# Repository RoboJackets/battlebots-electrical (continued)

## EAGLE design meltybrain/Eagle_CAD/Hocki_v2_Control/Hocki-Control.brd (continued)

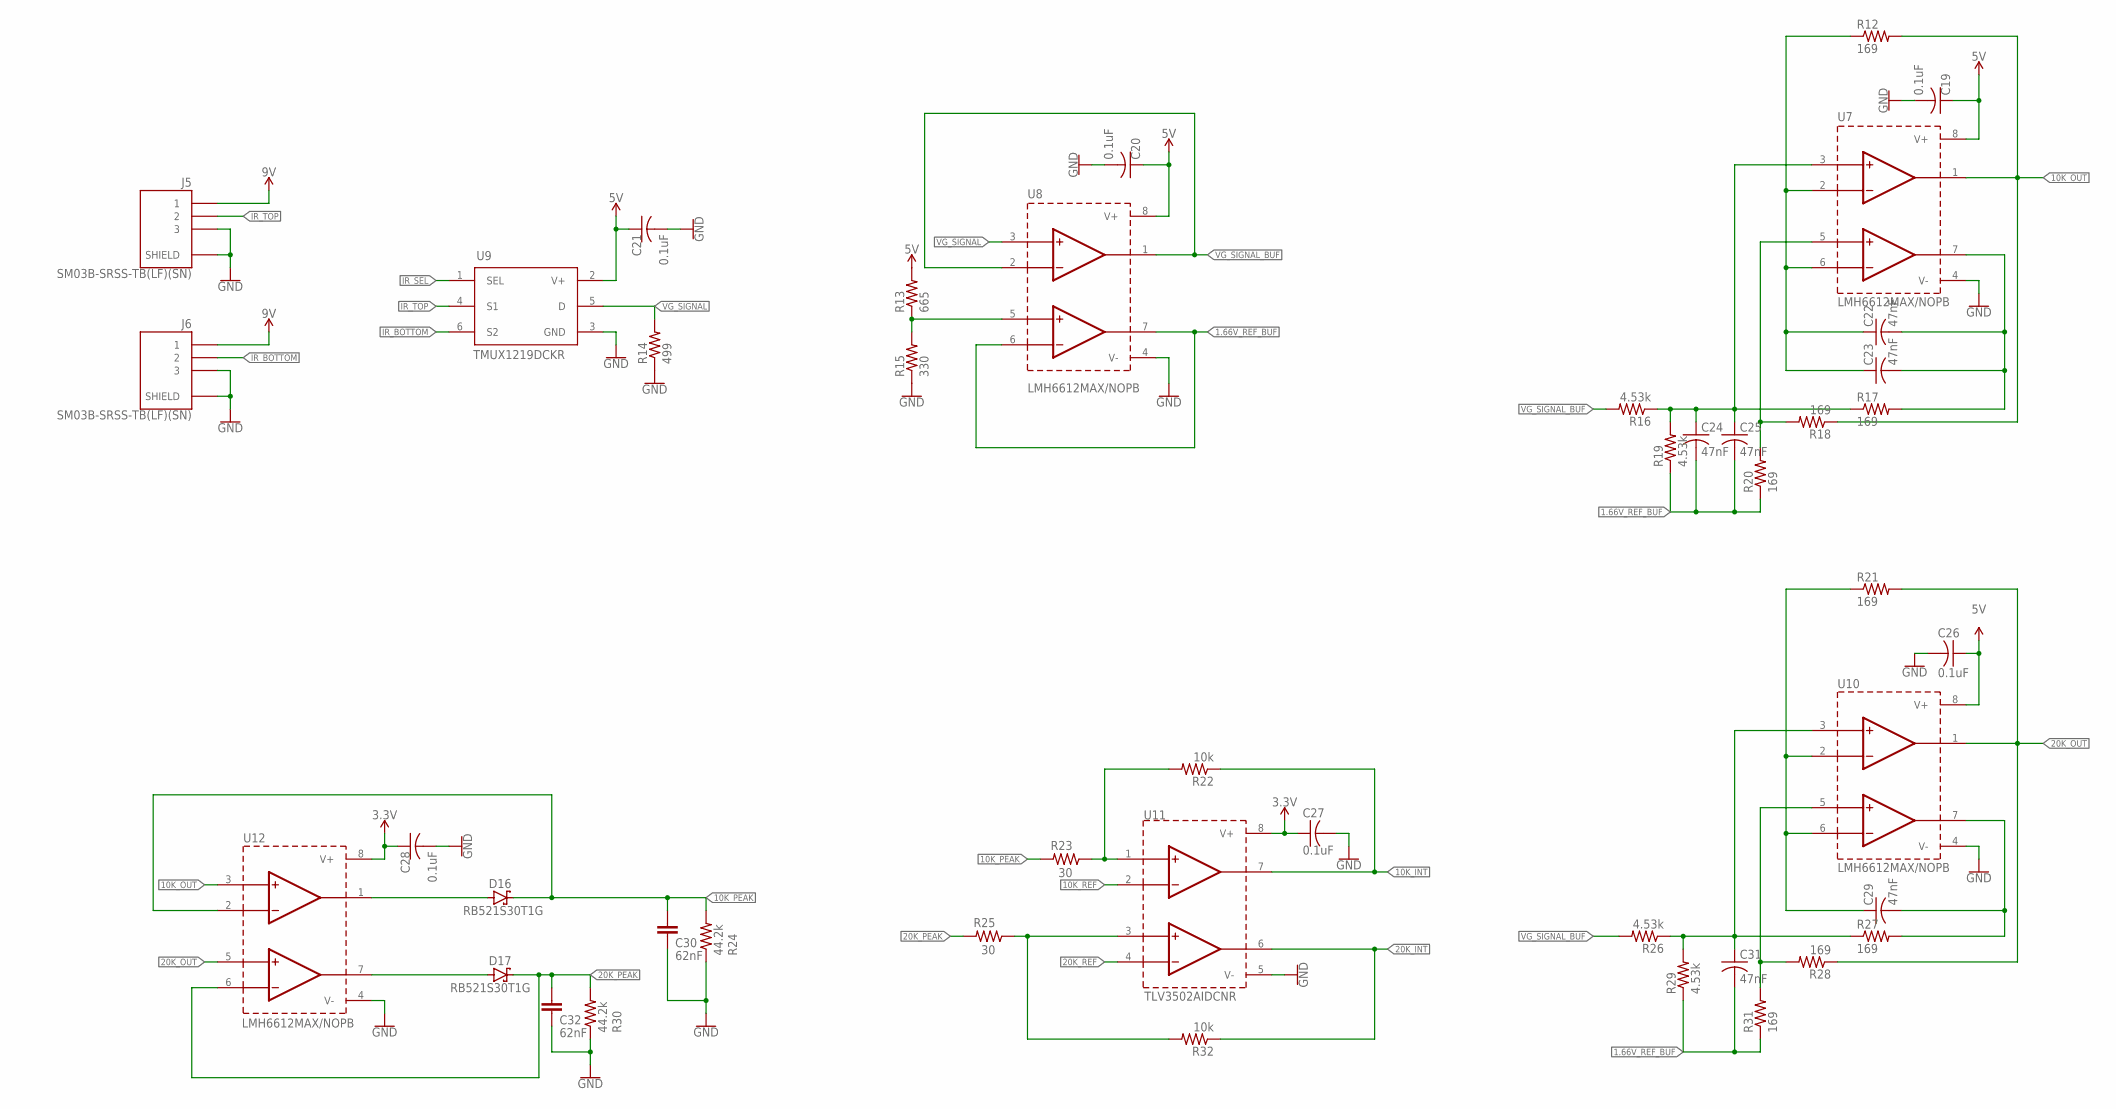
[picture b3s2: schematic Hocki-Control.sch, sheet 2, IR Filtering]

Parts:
C19, C20, C21, C26, C27, C28: 0.1uF; C0603
C22, C23, C24, C25, C29, C31: 47nF; C1206
C30, C32: 62nF; BFC241646203
D16, D17: RB521S30T1G; SOD-523
J5, J6: SM03B-SRSS-TB(LF)(SN)
R12, R17, R18, R20, R21, R27, R28, R31: 169; R0603
R13: 665; R0603
R14: 499; R0603
R15: 330; R0603
R16, R19, R26, R29: 4.53k; R0603
R22, R32: 10k; R0603
R23, R25: 30; R0603
R24, R30: 44.2k; R0603
U7, U8, U10, U12: LMH6612MAX/NOPB; 8-SOIC
U9: TMUX1219DCKR; SOT-363
U11: TLV3502AIDCNR; SOT-23-8

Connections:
1.6V_REF: R13.1, R15.2, U8.5 (INB+)
1.66V_REF_BUF: C24.2, C25.2, C31.2, R19.1, R20.1, R29.1, R31.1, U8.6 (INB-), U8.7 (OUTB)
3.3V: C27.1, C28.1, U11.8 (V+), U12.8 (V+); also elsewhere on the board
5V: C19.1, C20.1, C21.1, C26.1, R13.2, U7.8 (V+), U8.8 (V+), U9.2 (V+), U10.8 (V+); also elsewhere on the board
9V: J5.1, J6.1; also elsewhere on the board
10K_FB: C22.2, C23.2, R17.2, U7.7 (OUTB)
10K_IN: C24.1, C25.1, R16.1, R17.1, R19.2, U7.3 (INA+)
10K_INT: R22.1, U11.7 (OUTA); also elsewhere on the board
10K_OUT: R12.2, R18.1, U7.1 (OUTA), U12.3 (INA+)
10K_PEAK: C30.1, D16.1 (C), R23.2, R24.2, U12.2 (INA-); also elsewhere on the board
10K_REF: U11.2 (INA-); also elsewhere on the board
20K_FB: C29.2, R27.2, U10.7 (OUTB)
20K_IN: C31.1, R26.1, R27.1, R29.2, U10.3 (INA+)
20K_INT: R32.1, U11.6 (OUTB); also elsewhere on the board
20K_OUT: R21.2, R28.1, U10.1 (OUTA), U12.5 (INB+)
20K_PEAK: C32.1, D17.1 (C), R25.2, R30.2, U12.6 (INB-); also elsewhere on the board
20K_REF: U11.4 (INB-); also elsewhere on the board
GND: C19.2, C20.2, C21.2, C26.2, C27.2, C28.2, C30.2, C32.2, J5.3, J5.S1 (SHIELD), J5.S2 (SHIELD), J6.3, J6.S1 (SHIELD), J6.S2 (SHIELD), R14.1, R15.1, R24.1, R30.1, U7.4 (V-), U8.4 (V-), U9.3 (GND), U10.4 (V-), U11.5 (V-), U12.4 (V-); also elsewhere on the board
IR_BOTTOM: J6.2, U9.6 (S2)
IR_SEL: U9.1 (SEL); also elsewhere on the board
IR_TOP: J5.2, U9.4 (S1)
unnamed: D16.2 (A), U12.1 (OUTA)
unnamed: C22.1, C23.1, R12.1, U7.2 (INA-), U7.6 (INB-)
unnamed: R22.2, R23.1, U11.1 (INA+)
unnamed: R25.1, R32.2, U11.3 (INB+)
unnamed: R18.2, R20.2, U7.5 (INB+)
unnamed: D17.2 (A), U12.7 (OUTB)
unnamed: C29.1, R21.1, U10.2 (INA-), U10.6 (INB-)
unnamed: R28.2, R31.2, U10.5 (INB+)
VG_SIGNAL: R14.2, U8.3 (INA+), U9.5 (D)
VG_SIGNAL_BUF: R16.2, R26.2, U8.1 (OUTA), U8.2 (INA-)

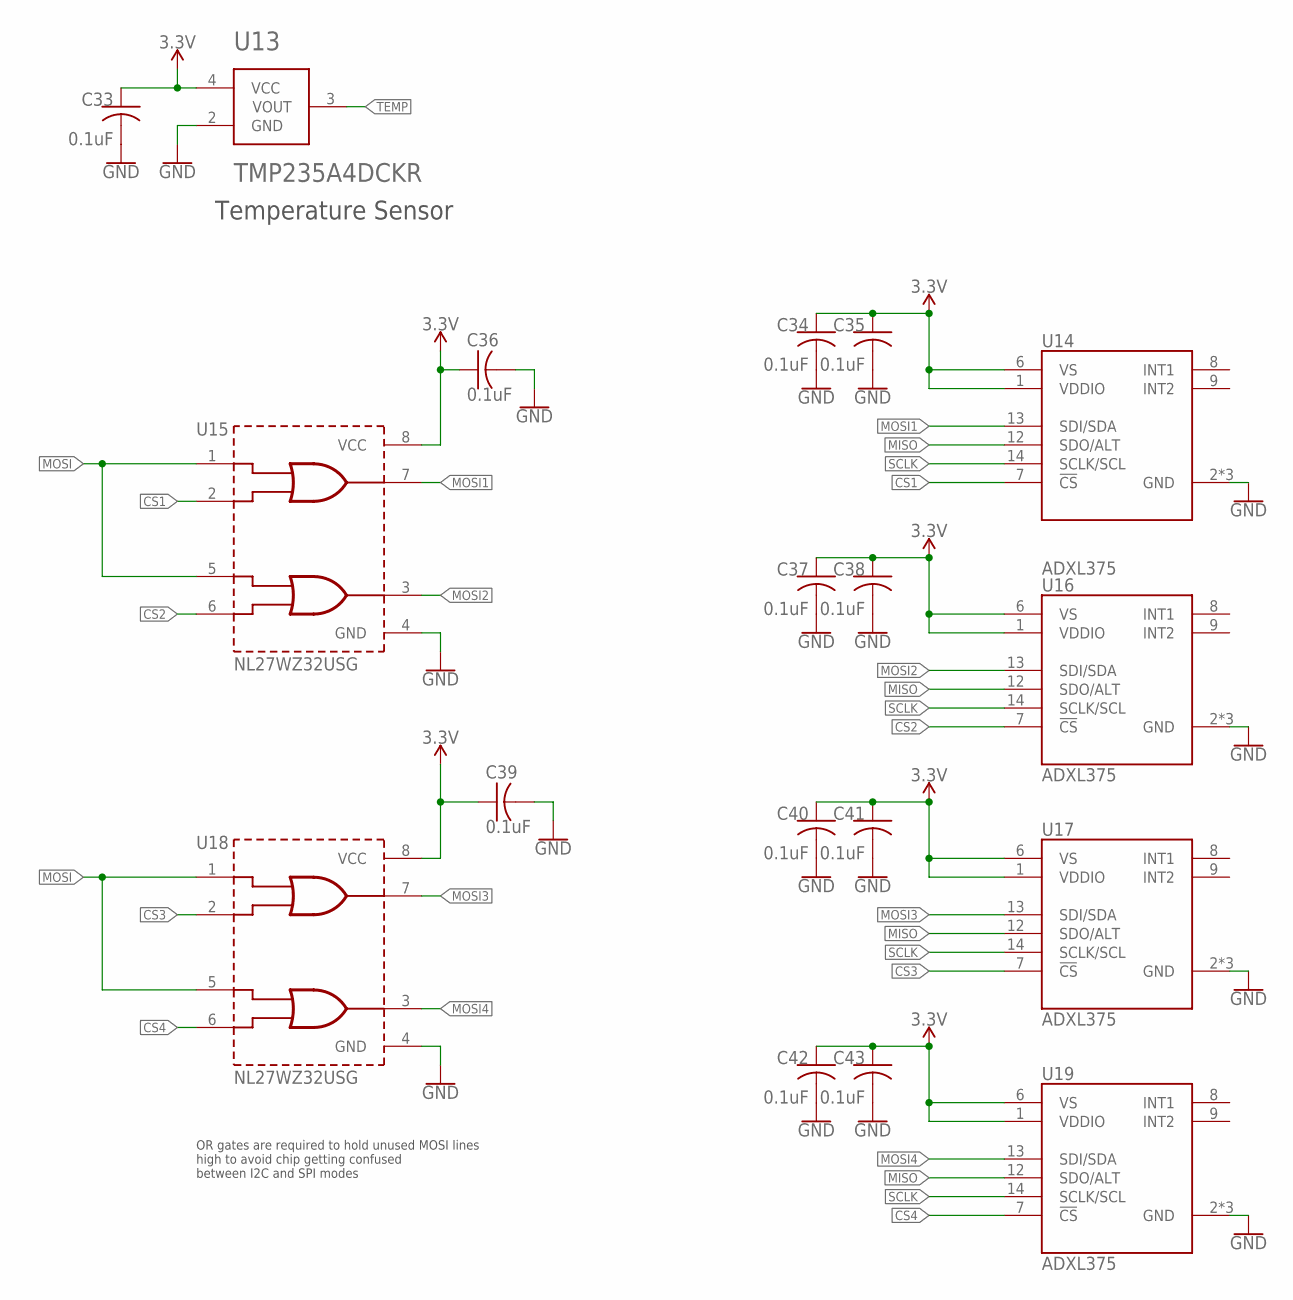
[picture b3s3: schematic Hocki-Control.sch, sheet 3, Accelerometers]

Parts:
C33, C34, C35, C36, C37, C38, C39, C40, C41, C42, C43: 0.1uF; C0603
U13: TMP235A4DCKR; SOT-353
U14, U16, U17, U19: ADXL375; 14-LGA
U15, U18: NL27WZ32USG; US8

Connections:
3.3V: C33.1, C34.1, C35.1, C36.1, C37.1, C38.1, C39.1, C40.1, C41.1, C42.1, C43.1, U13.4 (VCC), U14.1 (VDDIO), U14.6 (VS), U15.8 (VCC), U16.1 (VDDIO), U16.6 (VS), U17.1 (VDDIO), U17.6 (VS), U18.8 (VCC), U19.1 (VDDIO), U19.6 (VS); also elsewhere on the board
CS1: U14.7 (!CS), U15.2 (B1); also elsewhere on the board
CS2: U15.6 (B2), U16.7 (!CS); also elsewhere on the board
CS3: U17.7 (!CS), U18.2 (B1); also elsewhere on the board
CS4: U18.6 (B2), U19.7 (!CS); also elsewhere on the board
GND: C33.2, C34.2, C35.2, C36.2, C37.2, C38.2, C39.2, C40.2, C41.2, C42.2, C43.2, U13.2 (GND), U14.2 (GND), U14.4 (GND), U14.5 (GND), U15.4 (GND), U16.2 (GND), U16.4 (GND), U16.5 (GND), U17.2 (GND), U17.4 (GND), U17.5 (GND), U18.4 (GND), U19.2 (GND), U19.4 (GND), U19.5 (GND); also elsewhere on the board
MISO: U14.12 (SDO/ALT), U16.12 (SDO/ALT), U17.12 (SDO/ALT), U19.12 (SDO/ALT); also elsewhere on the board
MOSI: U15.1 (A1), U15.5 (A2), U18.1 (A1), U18.5 (A2); also elsewhere on the board
MOSI1: U14.13 (SDI/SDA), U15.7 (Y1)
MOSI2: U15.3 (Y2), U16.13 (SDI/SDA)
MOSI3: U17.13 (SDI/SDA), U18.7 (Y1)
MOSI4: U18.3 (Y2), U19.13 (SDI/SDA)
SCLK: U14.14 (SCLK/SCL), U16.14 (SCLK/SCL), U17.14 (SCLK/SCL), U19.14 (SCLK/SCL); also elsewhere on the board
TEMP: U13.3 (VOUT); also elsewhere on the board

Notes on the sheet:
OR gates are required to hold unused MOSI lines high to avoid chip getting confused between I2C and SPI modes
Temperature Sensor

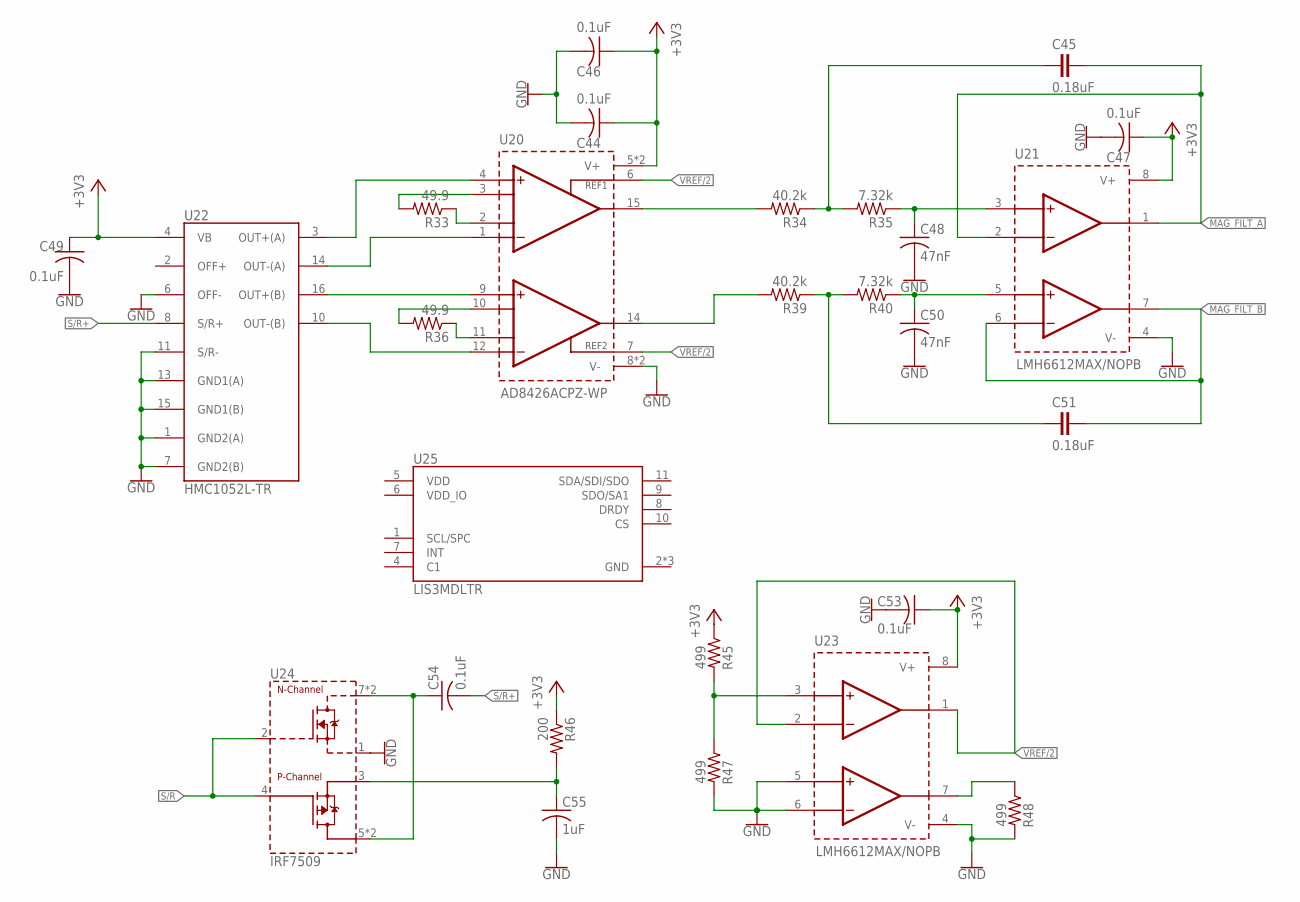
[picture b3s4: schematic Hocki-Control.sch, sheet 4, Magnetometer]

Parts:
C44, C46, C47, C49, C53, C54: 0.1uF; C0603
C45, C51: 0.18uF; ECH-U1H184GX9
C48, C50: 47nF; C1206
C55: 1uF; C0603
R33, R36: 49.9; R0603
R34, R39: 40.2k; R0603
R35, R40: 7.32k; R0603
R45, R47, R48: 499; R0603
R46: 200; R0603
U20: AD8426ACPZ-WP; 16LFCSP
U21, U23: LMH6612MAX/NOPB; 8-SOIC
U22: HMC1052L-TR; 16-LCC
U24: IRF7509; MICRO8
U25: LIS3MDLTR; LGA-12_2X2X1_STM

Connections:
+3V3: C44.1, C46.1, C47.1, C49.1, C53.1, R45.1, R46.1, U20.5 (V+), U20.16 (V+), U21.8 (V+), U22.4 (VB), U23.8 (V+); also elsewhere on the board
GND: C44.2, C46.2, C47.2, C48.2, C49.2, C50.2, C53.2, C55.2, R47.2, R48.2, U20.8 (V-), U20.13 (V-), U21.4 (V-), U22.1 (GND2(A)), U22.6 (OFF-), U22.7 (GND2(B)), U22.11 (S/R-), U22.13 (GND1(A)), U22.15 (GND1(B)), U23.4 (V-), U23.5 (INB+), U23.6 (INB-), U24.1 (S1); also elsewhere on the board
MAG_FILT_A: C45.2, U21.1 (OUTA), U21.2 (INA-); also elsewhere on the board
MAG_FILT_B: C51.2, U21.6 (INB-), U21.7 (OUTB); also elsewhere on the board
unnamed: C54.1, U24.5 (D2), U24.6 (D2), U24.7 (D1), U24.8 (D1)
unnamed: R45.2, R47.1, U23.3 (INA+)
unnamed: R48.1, U23.7 (OUTB)
unnamed: C45.1, R34.1, R35.2
unnamed: C48.1, R35.1, U21.3 (INA+)
unnamed: C51.1, R39.1, R40.2
unnamed: C50.1, R40.1, U21.5 (INB+)
unnamed: U20.4 (INA+), U22.3 (OUT+(A))
unnamed: U20.1 (INA-), U22.14 (OUT-(A))
unnamed: U20.9 (INB+), U22.16 (OUT+(B))
unnamed: U20.12 (INB-), U22.10 (OUT-(B))
unnamed: R39.2, U20.14 (OUTB)
unnamed: R34.2, U20.15 (OUTA)
unnamed: R33.2, U20.3 (RGA+)
unnamed: R33.1, U20.2 (RGA-)
unnamed: R36.2, U20.10 (RGB+)
unnamed: R36.1, U20.11 (RGB-)
S/R: U24.2 (G1), U24.4 (G2); also elsewhere on the board
S/R+: C54.2, U22.8 (S/R+)
VREF/2: U20.6 (REFA), U20.7 (REFB), U23.1 (OUTA), U23.2 (INA-)
VSR: C55.1, R46.2, U24.3 (S2)

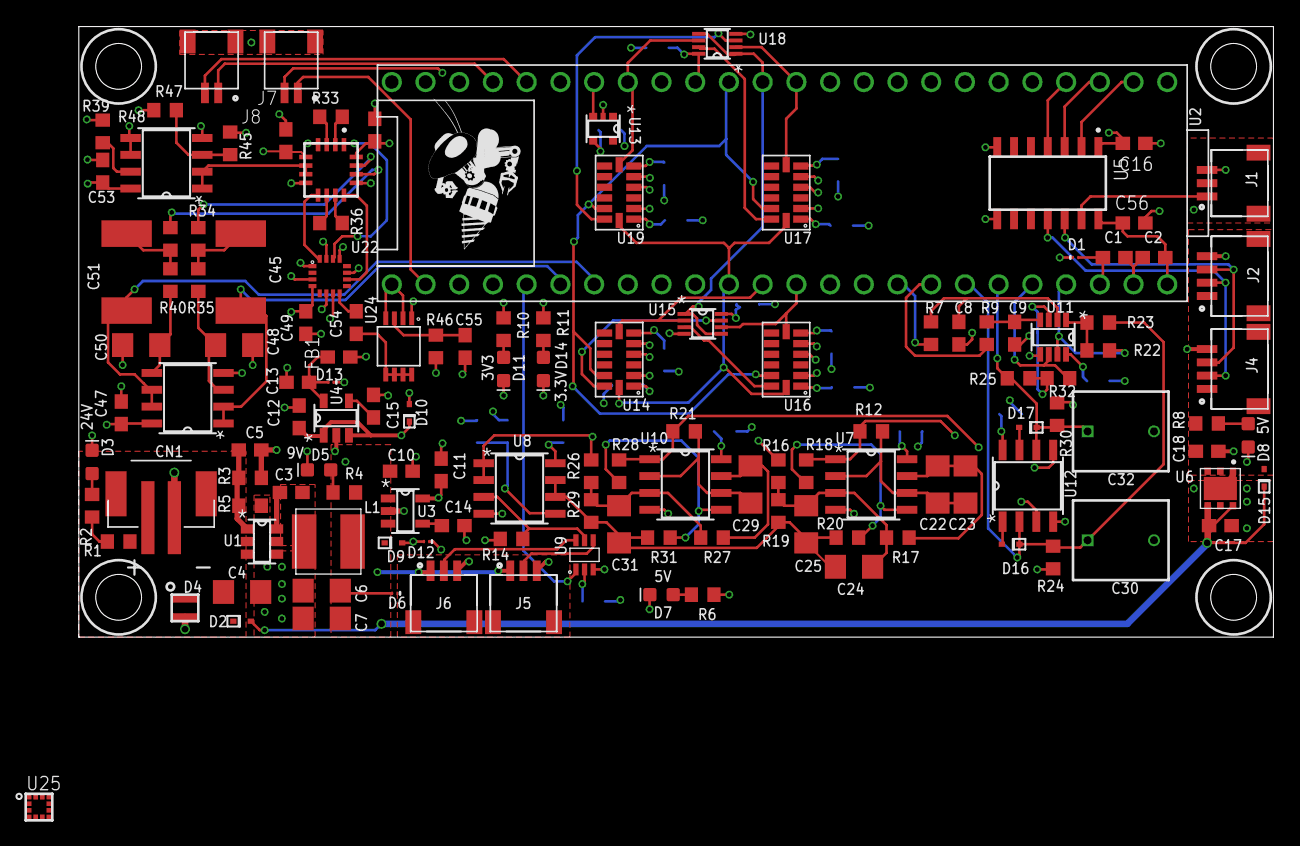
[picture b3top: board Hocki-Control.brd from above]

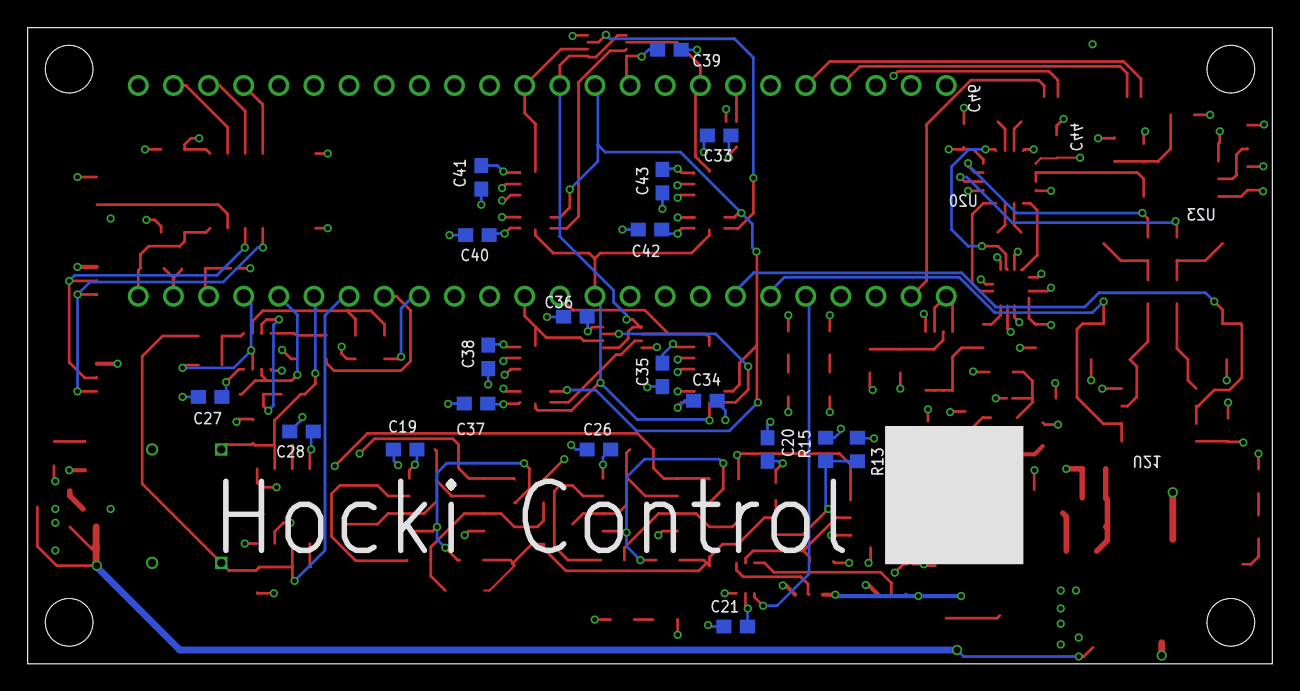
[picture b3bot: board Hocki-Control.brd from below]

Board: 4 copper layers, 90.0 x 46.0 mm, 150 parts (19 on the bottom side), 94 nets.

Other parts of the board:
U$2: ROBOBUZZ_0.6X

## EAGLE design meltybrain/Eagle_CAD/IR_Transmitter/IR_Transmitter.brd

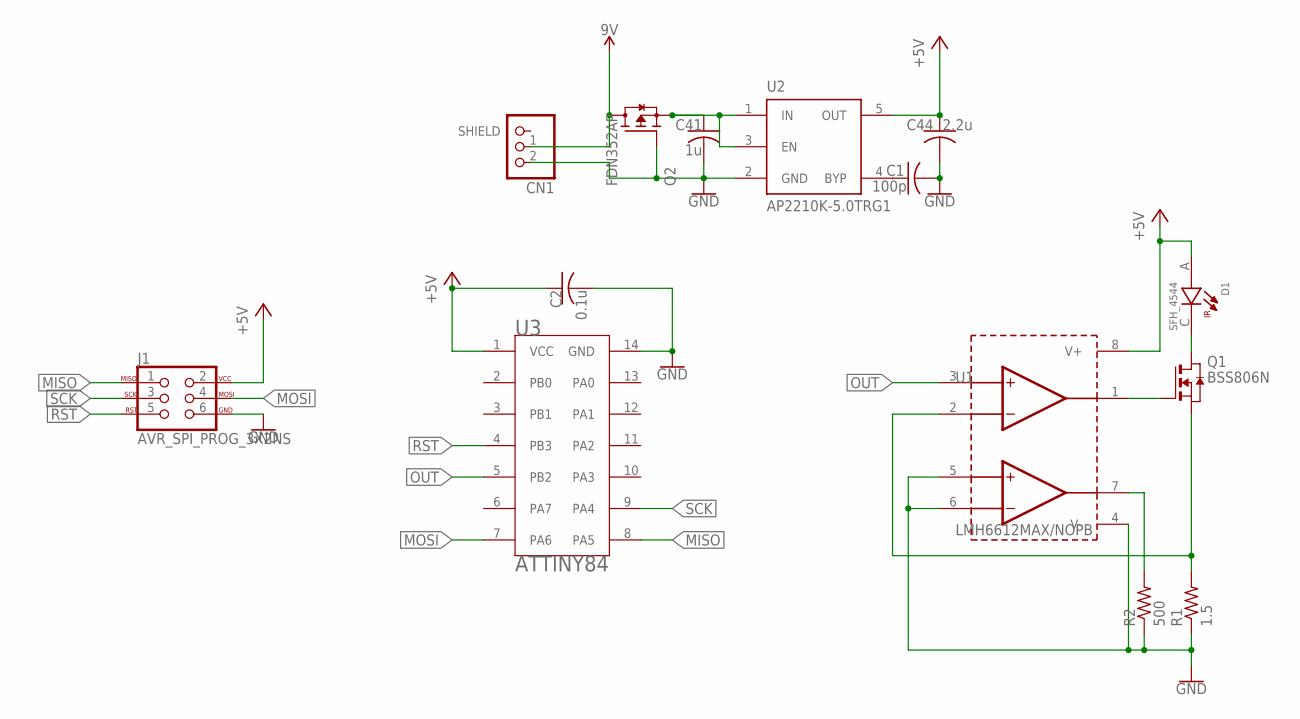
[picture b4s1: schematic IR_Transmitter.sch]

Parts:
C1: 100p; C0603
C2: 0.1u; C0603
C41: 1u; C0603
C44: 2.2u; C0603
CN1: JST_2PIN-SMT-RA; JST-PH-2-SMT-RA
D1: SFH_4544; DIO_SFH_4544
J1: AVR_SPI_PROG_3X2NS; 2X3-NS
Q1: BSS806N; SOT-23-3
Q2: FDN352AP; SSOT-3
R1: 1.5; R0805
R2: 500; R0603
U1: LMH6612MAX/NOPB; 8-SOIC
U2: AP2210K-5.0TRG1; SOT-23-5
U3: ATTINY84; SOIC-14

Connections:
9V: CN1.1 (2), Q2.3 (D)
+5V: C2.1, C44.1, D1.A, J1.2, U1.8 (V+), U2.5 (OUT), U3.1 (VCC)
GND: C1.2, C2.2, C41.2, C44.2, CN1.2 (1), J1.6, Q2.1 (G), R1.1, R2.1, U1.4 (V-), U1.5 (INB+), U1.6 (INB-), U2.2 (GND), U3.14 (GND)
MISO: J1.1, U3.8 (PA5)
MOSI: J1.4, U3.7 (PA6)
unnamed: Q1.2 (S), R1.2, U1.2 (INA-)
unnamed: Q1.1 (G), U1.1 (OUTA)
unnamed: R2.2, U1.7 (OUTB)
unnamed: D1.C, Q1.3 (D)
unnamed: C1.1, U2.4 (BYP)
unnamed: C41.1, Q2.2 (S), U2.1 (IN), U2.3 (EN)
OUT: U1.3 (INA+), U3.5 (PB2)
RST: J1.5, U3.4 (PB3)
SCK: J1.3, U3.9 (PA4)

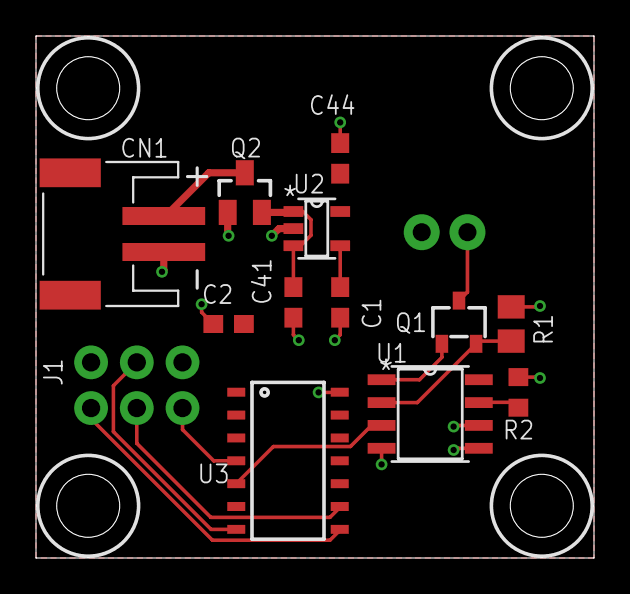
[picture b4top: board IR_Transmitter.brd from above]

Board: 2 copper layers, 31.0 x 29.0 mm, 14 parts (1 on the bottom side), 14 nets.

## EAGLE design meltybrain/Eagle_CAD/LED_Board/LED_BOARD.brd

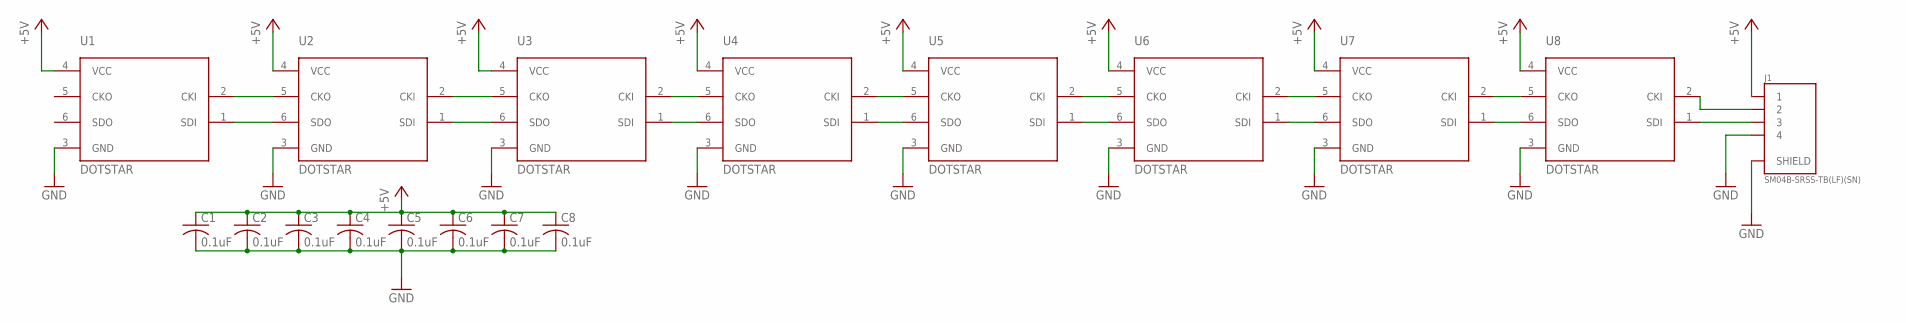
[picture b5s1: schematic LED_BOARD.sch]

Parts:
C1, C2, C3, C4, C5, C6, C7, C8: 0.1uF; C0603
J1: SM04B-SRSS-TB(LF)(SN)
U1, U2, U3, U4, U5, U6, U7, U8: DOTSTAR; RGBLED5050

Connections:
+5V: C1.1, C2.1, C3.1, C4.1, C5.1, C6.1, C7.1, C8.1, J1.1, U1.4 (VCC), U2.4 (VCC), U3.4 (VCC), U4.4 (VCC), U5.4 (VCC), U6.4 (VCC), U7.4 (VCC), U8.4 (VCC)
GND: C1.2, C2.2, C3.2, C4.2, C5.2, C6.2, C7.2, C8.2, J1.4, J1.S1 (SHIELD), J1.S2 (SHIELD), U1.3 (GND), U2.3 (GND), U3.3 (GND), U4.3 (GND), U5.3 (GND), U6.3 (GND), U7.3 (GND), U8.3 (GND)
unnamed: U1.2 (CKI), U2.5 (CKO)
unnamed: U1.1 (SDI), U2.6 (SDO)
unnamed: U2.2 (CKI), U3.5 (CKO)
unnamed: U2.1 (SDI), U3.6 (SDO)
unnamed: U3.2 (CKI), U4.5 (CKO)
unnamed: U3.1 (SDI), U4.6 (SDO)
unnamed: U4.2 (CKI), U5.5 (CKO)
unnamed: U4.1 (SDI), U5.6 (SDO)
unnamed: U5.2 (CKI), U6.5 (CKO)
unnamed: U5.1 (SDI), U6.6 (SDO)
unnamed: U6.2 (CKI), U7.5 (CKO)
unnamed: U6.1 (SDI), U7.6 (SDO)
unnamed: U7.2 (CKI), U8.5 (CKO)
unnamed: U7.1 (SDI), U8.6 (SDO)
unnamed: J1.2, U8.2 (CKI)
unnamed: J1.3, U8.1 (SDI)

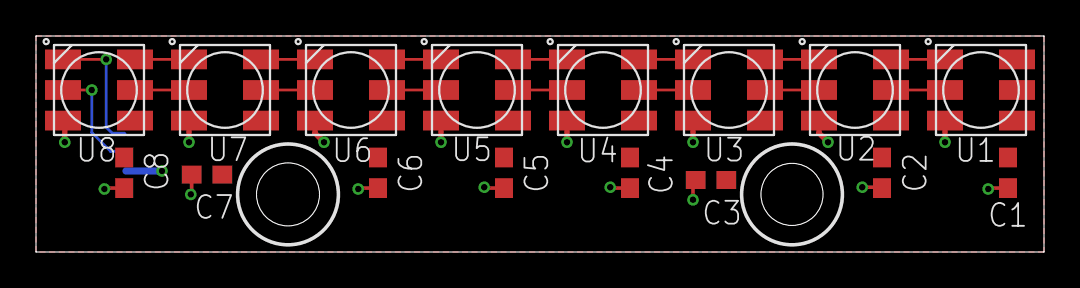
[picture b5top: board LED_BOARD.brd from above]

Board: 2 copper layers, 56.0 x 12.0 mm, 17 parts (1 on the bottom side), 18 nets.

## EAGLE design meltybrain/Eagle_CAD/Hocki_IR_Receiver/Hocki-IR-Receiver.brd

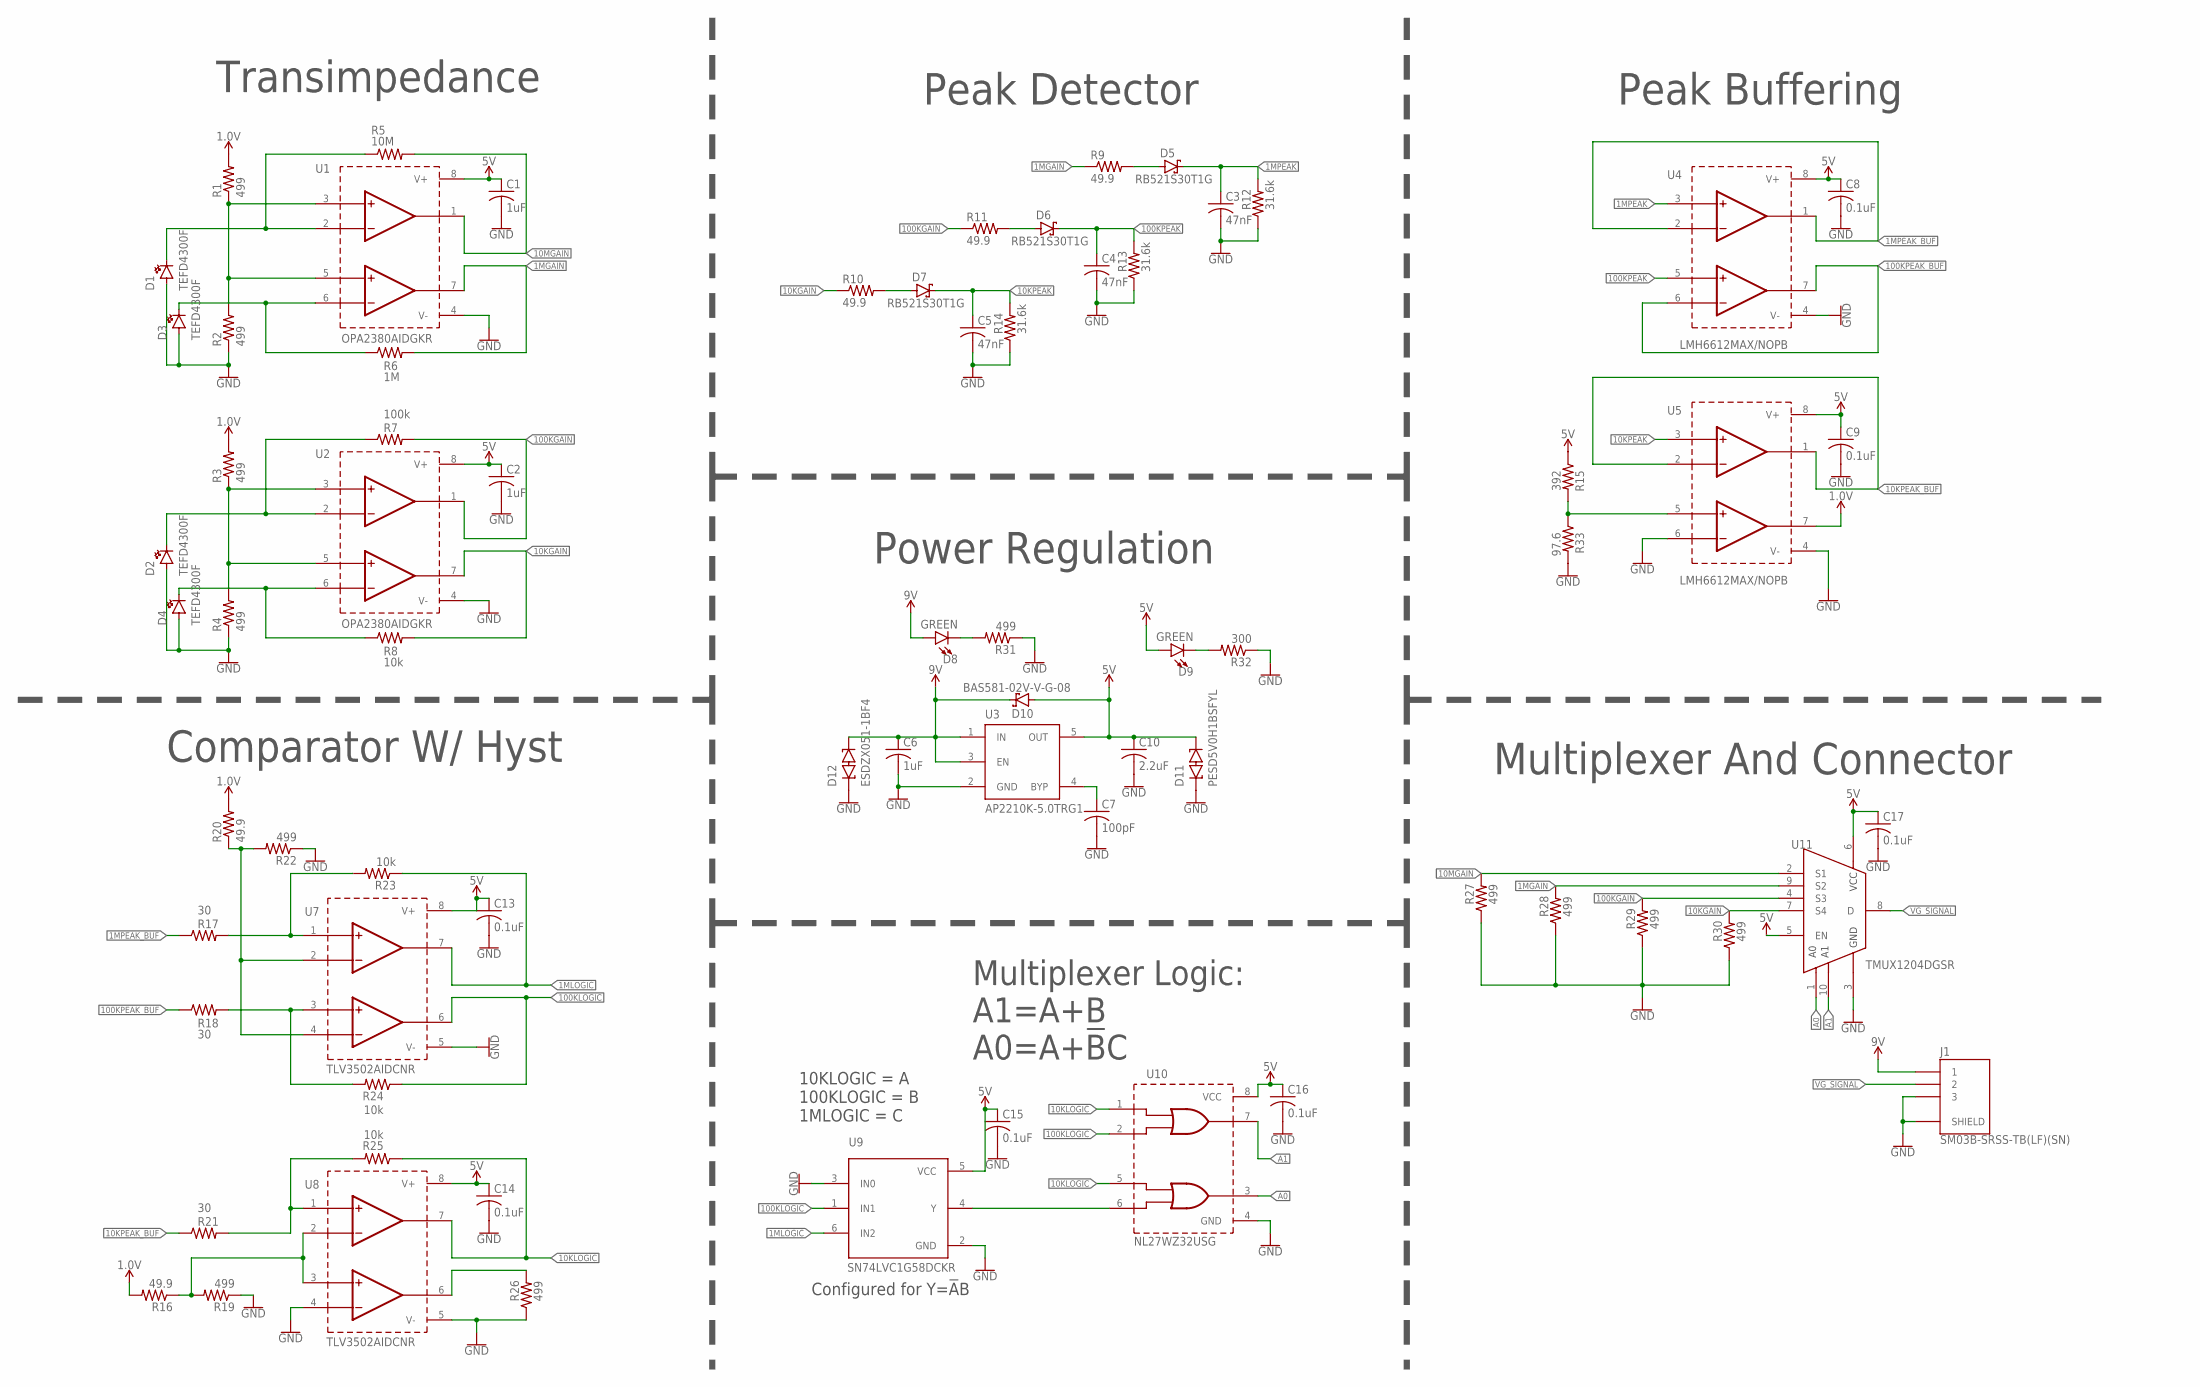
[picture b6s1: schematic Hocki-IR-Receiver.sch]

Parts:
C1, C2, C6: 1uF; C0603
C3, C4, C5: 47nF; C1206
C7: 100pF; C0603
C8, C9, C13, C14, C15, C16, C17: 0.1uF; C0603
C10: 2.2uF; C0603
D1, D2, D3, D4: TEFD4300F
D5, D6, D7: RB521S30T1G; SOD-523
D8, D9: GREEN; LED-0603
D10: BAS581-02V-V-G-08; SOD-523
D11: PESD5V0H1BSFYL; DSN0603-2
D12: ESDZX051-1BF4; DSN0603-2
J1: SM03B-SRSS-TB(LF)(SN)
R1, R2, R3, R4, R19, R22, R26, R27, R28, R29, R30, R31: 499; R0603
R5: 10M; R1206
R6: 1M; R0603
R7: 100k; R0603
R8, R23, R24, R25: 10k; R0603
R9, R10, R11, R16, R20: 49.9; R0603
R12, R13, R14: 31.6k; R0603
R15: 392; R0603
R17, R18, R21: 30; R0603
R32: 300; R0603
R33: 97.6; R0603
U1, U2: OPA2380AIDGKR; 8-VSSOP
U3: AP2210K-5.0TRG1; SOT-23-5
U4, U5: LMH6612MAX/NOPB; 8-SOIC
U7, U8: TLV3502AIDCNR; SOT-23-8
U9: SN74LVC1G58DCKR; SC-70-6
U10: NL27WZ32USG; US8
U11: TMUX1204DGSR; 10-VSSOP

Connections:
1.0V: R1.2, R3.2, R16.2, R20.2, U5.7 (OUTB)
1MGAIN: R6.2, R9.1, R28.2, U1.7 (OUTB), U11.9 (S2)
1MLOGIC: R23.1, U7.7 (OUTA), U9.6 (IN2)
1MPEAK: C3.1, D5.1 (C), R12.2, U4.3 (INA+)
1MPEAK_BUF: R17.1, U4.1 (OUTA), U4.2 (INA-)
5V: C1.1, C2.1, C8.1, C9.1, C10.1, C13.1, C14.1, C15.1, C16.1, C17.1, D9.A, D10.2 (A), D11.C2, R15.1, U1.8 (V+), U2.8 (V+), U3.5 (OUT), U4.8 (V+), U5.8 (V+), U7.8 (V+), U8.8 (V+), U9.5 (VCC), U10.8 (VCC), U11.5 (EN), U11.6 (VCC)
9V: C6.1, D8.A, D10.1 (C), D12.C2, J1.1, U3.1 (IN), U3.3 (EN)
10KGAIN: R8.2, R10.1, R30.2, U2.7 (OUTB), U11.7 (S4)
10KLOGIC: R25.1, U8.7 (OUTA), U10.1 (A1), U10.5 (A2)
10KPEAK: C5.1, D7.1 (C), R14.2, U5.3 (INA+)
10KPEAK_BUF: R21.1, U5.1 (OUTA), U5.2 (INA-)
10MGAIN: R5.2, R27.2, U1.1 (OUTA), U11.2 (S1)
100KGAIN: R7.2, R11.1, R29.2, U2.1 (OUTA), U11.4 (S3)
100KLOGIC: R24.1, U7.6 (OUTB), U9.1 (IN1), U10.2 (B1)
100KPEAK: C4.1, D6.1 (C), R13.2, U4.5 (INB+)
100KPEAK_BUF: R18.1, U4.6 (INB-), U4.7 (OUTB)
A0: U10.3 (Y2), U11.1 (A0)
A1: U10.7 (Y1), U11.10 (A1)
GND: C1.2, C2.2, C3.2, C4.2, C5.2, C6.2, C7.2, C8.2, C9.2, C10.2, C13.2, C14.2, C15.2, C16.2, C17.2, D1.1 (ANODE), D2.1 (ANODE), D3.1 (ANODE), D4.1 (ANODE), D11.C1, D12.C1, J1.3, J1.S1 (SHIELD), J1.S2 (SHIELD), R2.1, R4.1, R12.1, R13.1, R14.1, R19.1, R22.1, R26.1, R27.1, R28.1, R29.1, R30.1, R31.1, R32.1, R33.2, U1.4 (V-), U2.4 (V-), U3.2 (GND), U4.4 (V-), U5.4 (V-), U5.6 (INB-), U7.5 (V-), U8.4 (INB-), U8.5 (V-), U9.2 (GND), U9.3 (IN0), U10.4 (GND), U11.3 (GND)
unnamed: D1.2 (CATHODE), R5.1, U1.2 (INA-)
unnamed: D6.2 (A), R11.2
unnamed: D3.2 (CATHODE), R6.1, U1.6 (INB-)
unnamed: D7.2 (A), R10.2
unnamed: R1.1, R2.2, U1.3 (INA+), U1.5 (INB+)
unnamed: D2.2 (CATHODE), R7.1, U2.2 (INA-)
unnamed: R26.2, U8.6 (OUTB)
unnamed: C7.1, U3.4 (BYP)
unnamed: U9.4 (Y), U10.6 (B2)
unnamed: D4.2 (CATHODE), R8.1, U2.6 (INB-)
unnamed: D9.C, R32.2
unnamed: R3.1, R4.2, U2.3 (INA+), U2.5 (INB+)
unnamed: R20.1, R22.2, U7.2 (INA-), U7.4 (INB-)
unnamed: R16.1, R19.2, U8.2 (INA-), U8.3 (INB+)
unnamed: R15.2, R33.1, U5.5 (INB+)
unnamed: R18.2, R24.2, U7.3 (INB+)
unnamed: D5.2 (A), R9.2
unnamed: R21.2, R25.2, U8.1 (INA+)
unnamed: R17.2, R23.2, U7.1 (INA+)
unnamed: D8.C, R31.2
VG_SIGNAL: J1.2, U11.8 (D)

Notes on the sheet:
Multiplexer Logic: A1=A+B A0=A+!B!C
Configured for Y=!A!B
10KLOGIC = A 100KLOGIC = B 1MLOGIC = C
Transimpedance
Peak Detector
Peak Buffering
Comparator W/ Hyst
Power Regulation
Multiplexer And Connector

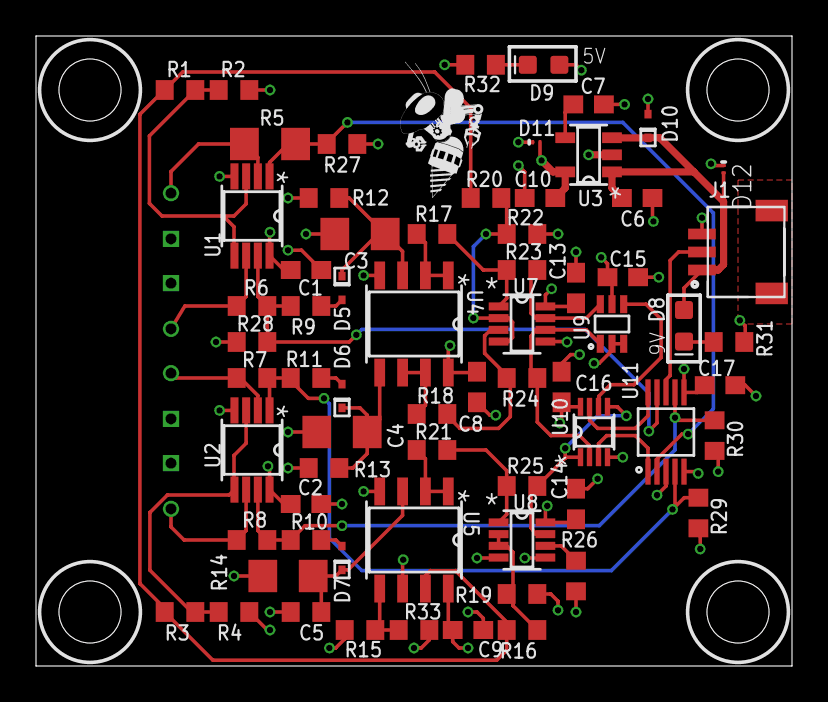
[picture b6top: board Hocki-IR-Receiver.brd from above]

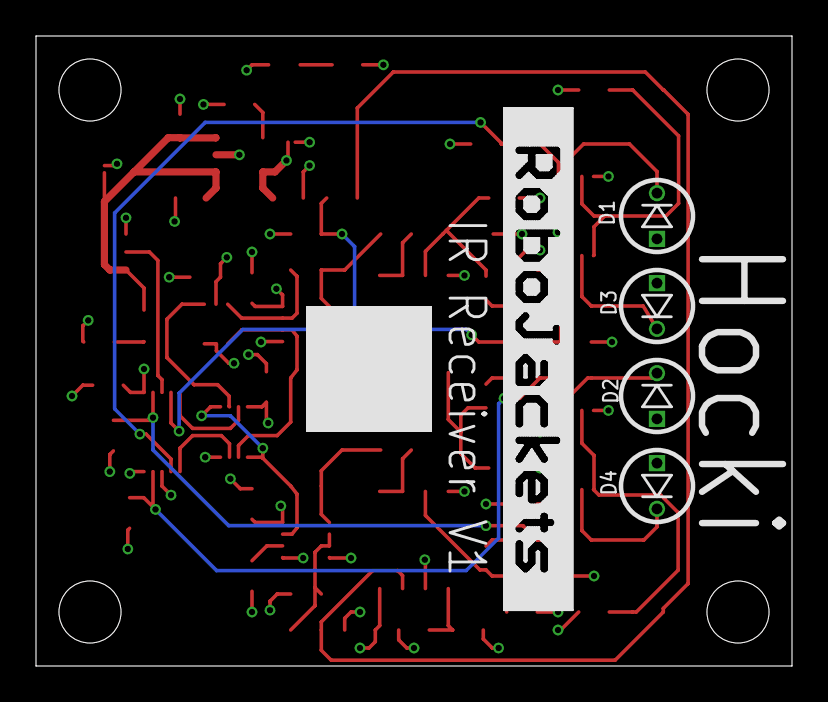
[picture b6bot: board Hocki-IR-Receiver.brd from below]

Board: 4 copper layers, 42.0 x 35.0 mm, 73 parts (5 on the bottom side), 40 nets.

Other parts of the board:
U$1: ROBOBUZZ_0.4X
U$2: ROBOJACKETS
